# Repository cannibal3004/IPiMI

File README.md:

# IPiMI

A simple board to allow you to connect a raspberry pi (or other micro controller) to the front panel connectors on a consumer PC Motherboard. Allow the connected device to control the power and reset buttons as well as read the state of the power and hdd leds from the motherboard.

**Totally untested**, designed with Gigabyte motherboards in mind. If you use this with another manufacturers board, you may need to modify the front panel connector.

# Gigabyte Front Panel Pinout:

# Schematic:

# PCB:

# 3D Render
## Front:

## Back:

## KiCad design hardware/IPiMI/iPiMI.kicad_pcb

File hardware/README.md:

# IPiMI PCB and Schematic Files

Designed with [KiCad](https://www.kicad.org)

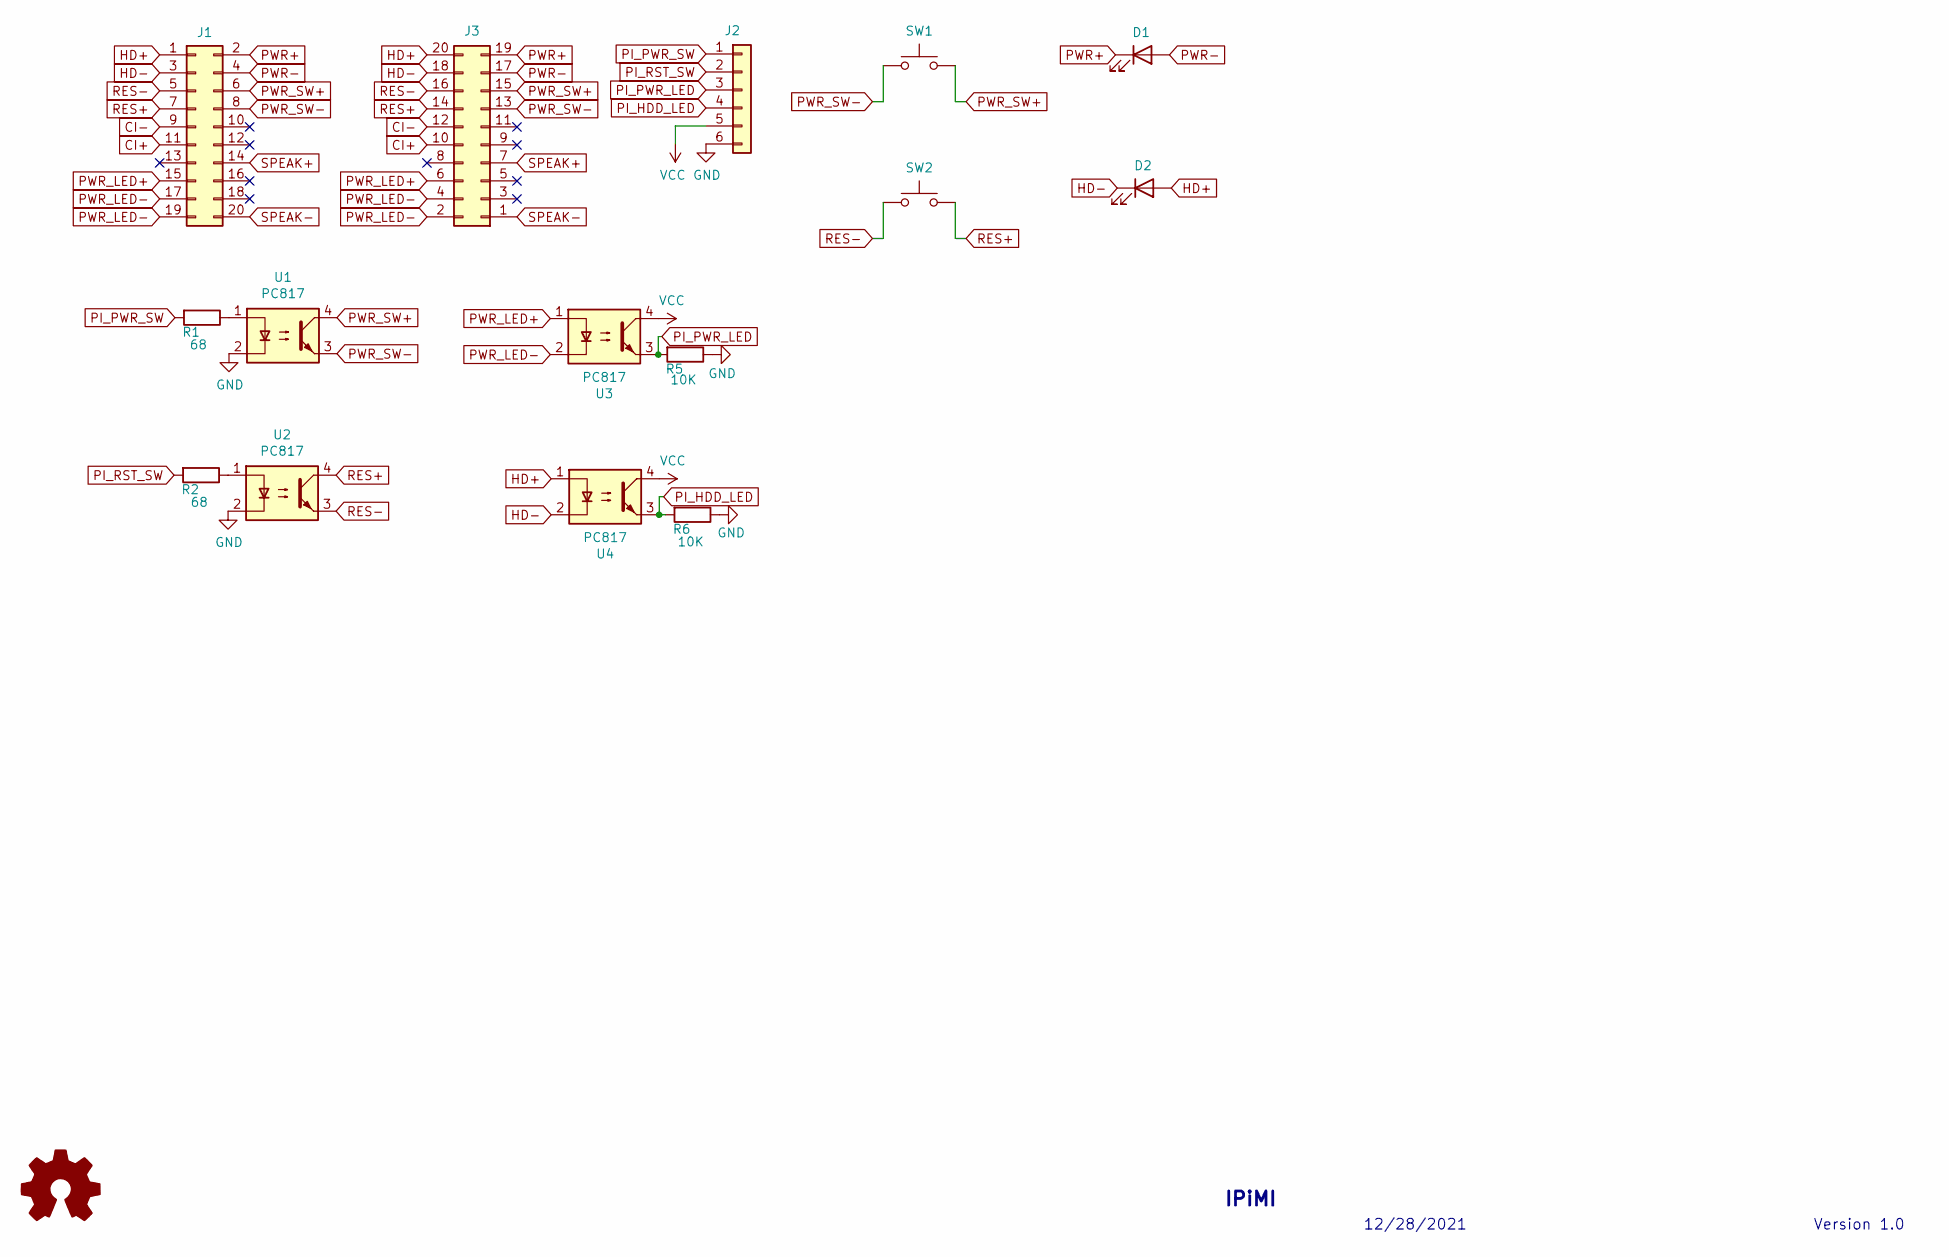
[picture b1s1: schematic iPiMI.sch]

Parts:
D1, D2: LED; LED_1206_3216Metric_Pad1.42x1.75mm_HandSolder
J1: Conn_02x10_Odd_Even; PinHeader_2x10_P2.54mm_Vertical
J2: Conn_01x06; PinHeader_1x06_P2.54mm_Horizontal
J3: Conn_02x10_Odd_Even; PinSocket_2x10_P2.54mm_Vertical
R1, R2: 68; R_1206_3216Metric_Pad1.30x1.75mm_HandSolder
R5, R6: 10K; R_1206_3216Metric_Pad1.30x1.75mm_HandSolder
SW1, SW2: SW_Push; SW_PUSH_6mm
U1, U2, U3, U4: PC817; DIP-4_W7.62mm

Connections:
+3V3: J2.5, U3.4, U4.4
CI+: J1.11, J3.10
CI-: J1.9, J3.12
GND: J2.6, R5.1, R6.1, U1.2, U2.2
HD+: D2.2 (A), J1.1, J3.20, U4.1
HD-: D2.1 (K), J1.3, J3.18, U4.2
unnamed: R1.1, U1.1
unnamed: R2.1, U2.1
PI_HDD_LED: J2.4, R6.2, U4.3
PI_PWR_LED: J2.3, R5.2, U3.3
PI_PWR_SW: J2.1, R1.2
PI_RST_SW: J2.2, R2.2
PWR+: D1.1 (K), J1.2, J3.19
PWR-: D1.2 (A), J1.4, J3.17
PWR_LED+: J1.15, J3.6, U3.1
PWR_LED-: J1.17, J1.19, J3.2, J3.4, U3.2
PWR_SW+: J1.6, J3.15, SW1.2, U1.4
PWR_SW-: J1.8, J3.13, SW1.1, U1.3
RES+: J1.7, J3.14, SW2.2, U2.4
RES-: J1.5, J3.16, SW2.1, U2.3
SPEAK+: J1.14, J3.7
SPEAK-: J1.20, J3.1

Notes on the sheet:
IPiMI
Version 1.0
12/28/2021

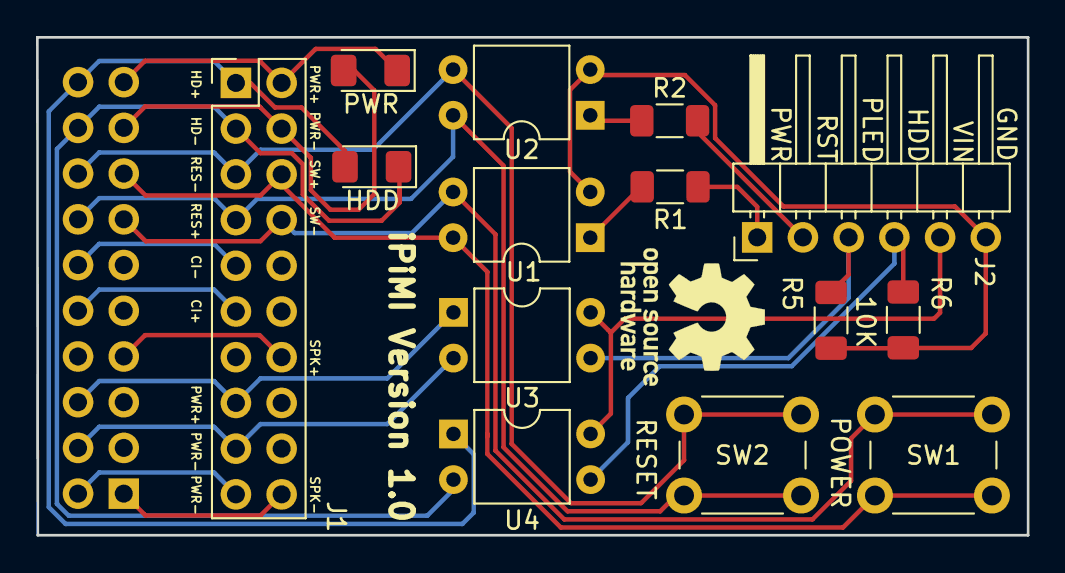
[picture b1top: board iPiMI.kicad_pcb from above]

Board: 2 copper layers, 55.0 x 27.7 mm, 15 parts (1 on the bottom side), 22 nets.

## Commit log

2021-12-28 Inital commit
2021-12-28 added images
2021-12-28 add images
2021-12-29 cleanup images
2021-12-29 update gerbers
2021-12-29 update pcb config
2021-12-29 initial arduino code started.
